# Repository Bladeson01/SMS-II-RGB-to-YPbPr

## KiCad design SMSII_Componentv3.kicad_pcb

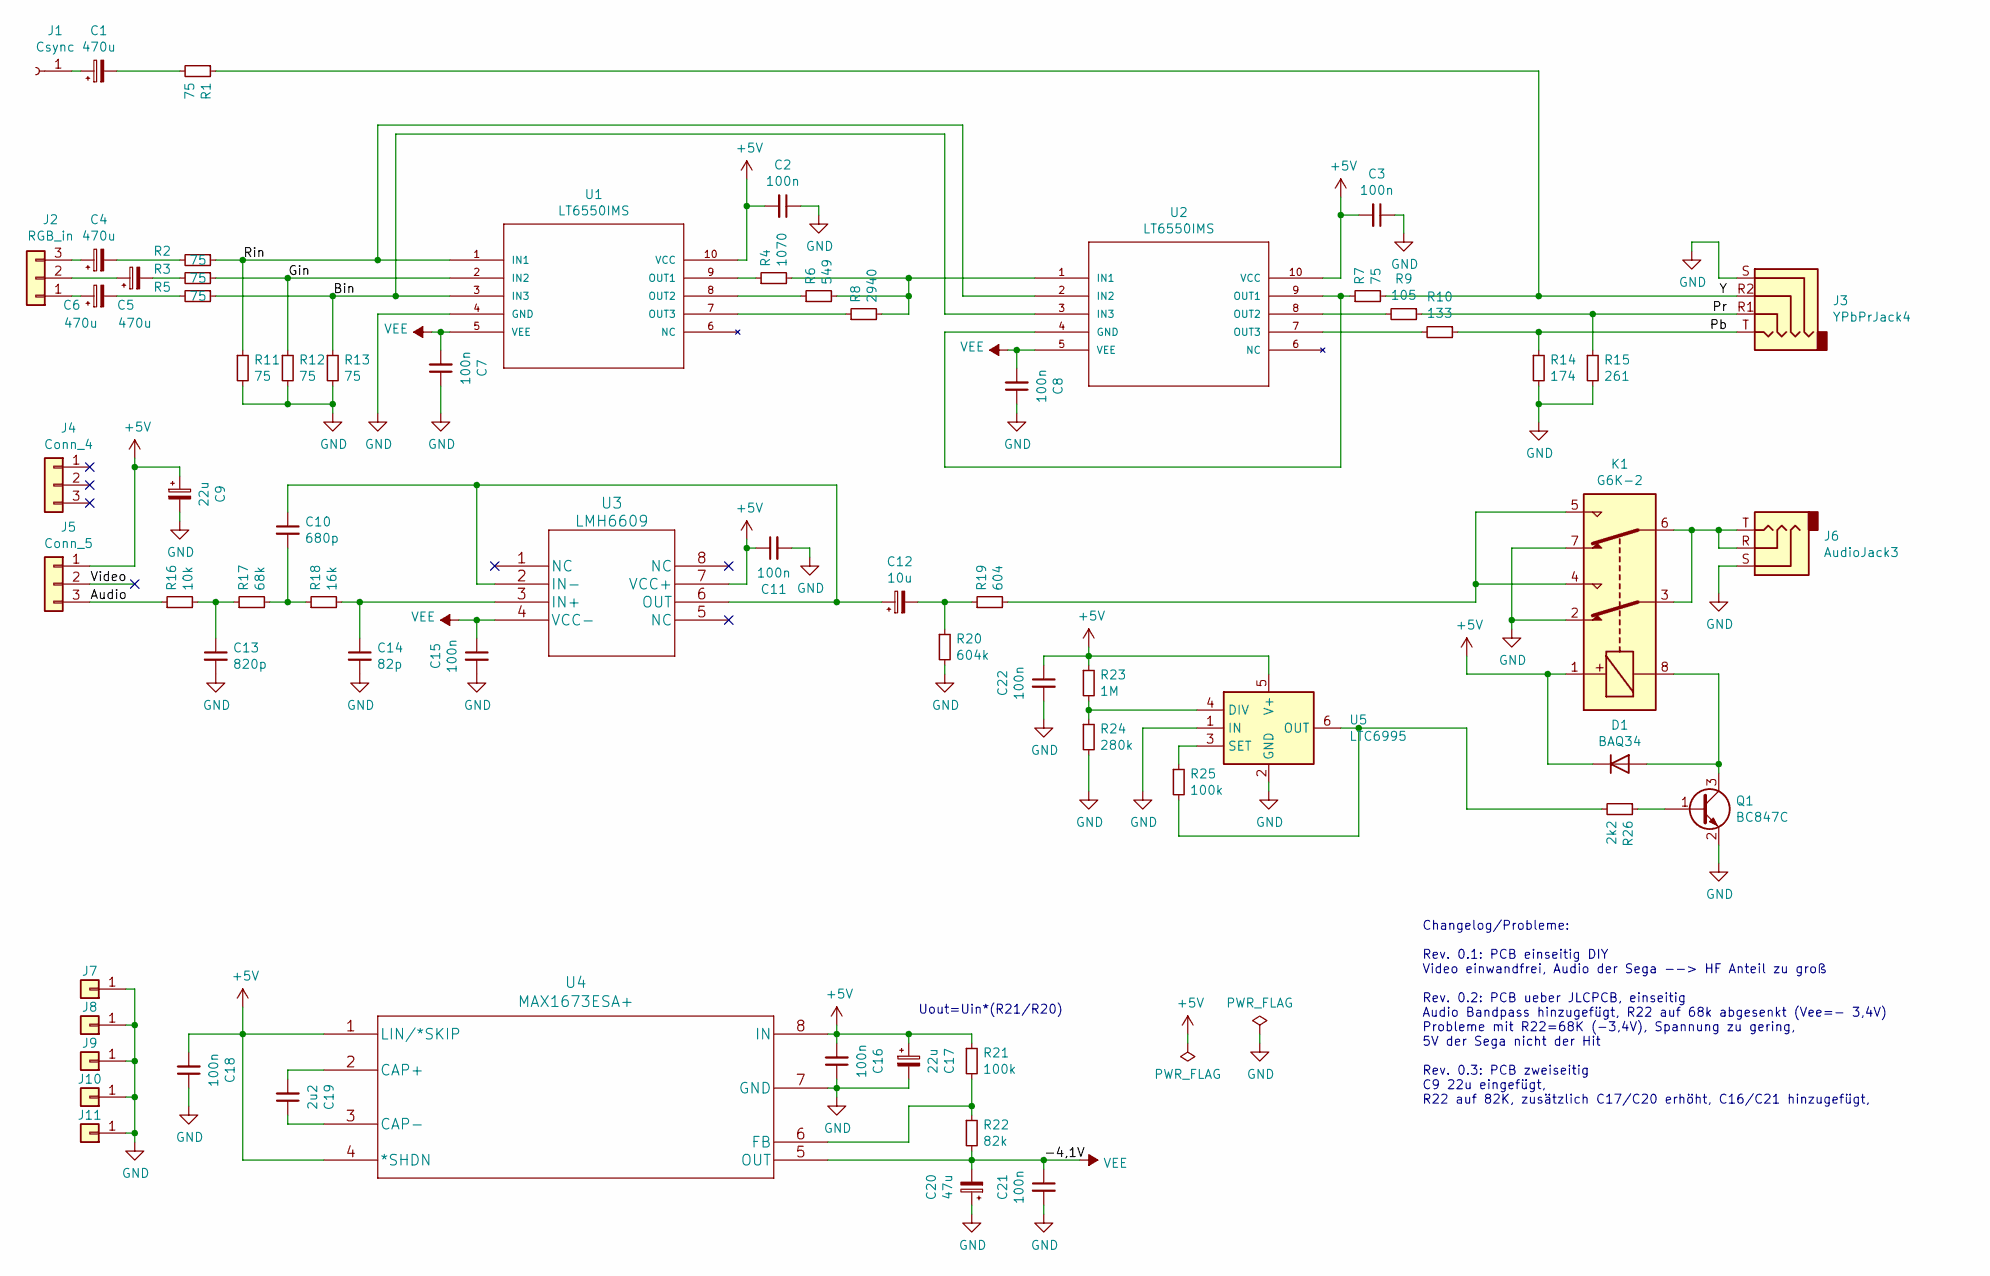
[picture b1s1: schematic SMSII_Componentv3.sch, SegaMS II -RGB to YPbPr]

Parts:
C1, C4, C5, C6: 470u; CP_Elec_6.3x7.7; LCSC C344072
C2, C3, C7, C8, C11, C15, C16, C18, C21, C22: 100n; C_0603_1608Metric_Pad1.05x0.95mm_HandSolder; LCSC C1591
C9, C17: 22u; CP_Elec_5x5.8; LCSC C336306
C10: 680p; C_0603_1608Metric_Pad1.05x0.95mm_HandSolder
C12: 10u; CP_Elec_4x5.8; LCSC C343907
C13: 820p; C_0603_1608Metric_Pad1.05x0.95mm_HandSolder
C14: 82p; C_0603_1608Metric_Pad1.05x0.95mm_HandSolder; LCSC C107056
C19: 2u2; C_0603_1608Metric_Pad1.05x0.95mm_HandSolder; LCSC C162273
C20: 47u; CP_Elec_6.3x5.8; LCSC C249507
D1: BAQ34; D_MiniMELF
J1: Csync; TestPoint_Pad_D2.0mm
J2: RGB_in; PinHeader_1x03_P2.54mm_Vertical
J3: YPbPrJack4; Jack_3.5mm_SMT_Lumberg_13
J4: Conn_4; PinHeader_1x03_P2.54mm_Vertical
J5: Conn_5; PinHeader_1x03_P2.54mm_Vertical
J6: AudioJack3; Jack_3.5mm_3p_SMT_Lumberg
J7, J8, J9, J10, J11: GND; PinHeader_1x01_P2.54mm_Vertical
K1: G6K-2; Relay_DPDT_Omron_G6K-2G-Y
Q1: BC847C; SOT-323_SC-70
R1, R2, R3, R5, R7, R11, R12, R13: 75; R_0603_1608Metric_Pad1.05x0.95mm_HandSolder; LCSC C218142
R4: 1070; R_0603_1608Metric_Pad1.05x0.95mm_HandSolder; LCSC C217842
R6: 549; R_0603_1608Metric_Pad1.05x0.95mm_HandSolder; LCSC C218072
R8: 2940; R_0603_1608Metric_Pad1.05x0.95mm_HandSolder; LCSC C217948
R9: 105; R_0603_1608Metric_Pad1.05x0.95mm_HandSolder; LCSC C217685
R10: 133; R_0603_1608Metric_Pad1.05x0.95mm_HandSolder; LCSC C217726
R14: 174; R_0603_1608Metric_Pad1.05x0.95mm_HandSolder; LCSC C217819
R15: 261; R_0603_1608Metric_Pad1.05x0.95mm_HandSolder; LCSC C217913
R16: 10k; R_0603_1608Metric_Pad1.05x0.95mm_HandSolder; LCSC C128781
R17: 68k; R_0603_1608Metric_Pad1.05x0.95mm_HandSolder; LCSC C425645
R18: 16k; R_0603_1608Metric_Pad1.05x0.95mm_HandSolder; LCSC C217760
R19: 604; R_0603_1608Metric_Pad1.05x0.95mm_HandSolder; LCSC C218096
R20: 604k; R_0603_1608Metric_Pad1.05x0.95mm_HandSolder; LCSC C218095
R21: 100k; R_0603_1608Metric_Pad1.05x0.95mm_HandSolder; LCSC C217682
R22: 82k; R_0603_1608Metric_Pad1.05x0.95mm_HandSolder; LCSC C218159
R23: 1M; R_0603_1608Metric_Pad1.05x0.95mm_HandSolder; LCSC C218095
R24: 280k; R_0603_1608Metric_Pad1.05x0.95mm_HandSolder; LCSC C218095
R25: 100k; R_0603_1608Metric_Pad1.05x0.95mm_HandSolder; LCSC C218095
R26: 2k2; R_0603_1608Metric_Pad1.05x0.95mm_HandSolder; LCSC C218095
U1, U2: LT6550IMS; MSOP-10_MS; LCSC C673138
U3: LMH6609; TL971ID; LCSC C1346629
U4: MAX1673ESA+; MAX1673ESA&plus_; LCSC C143369
U5: LTC6995; TSOT-23-6

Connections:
+5V: C2.2, C3.2, C9.1, C11.1, C16.2, C17.1, C18.2, C22.1, D1.1 (K), J5.1, K1.1, R21.1, R23.1, U1.10 (VCC), U2.10 (VCC), U3.7 (VCC+), U4.1 (LIN/*SKIP), U4.4 (*SHDN), U4.8 (IN), U5.5 (V+)
/Audio: J5.3, R16.1
/Bin: R5.1, R13.1, U1.3 (IN3), U2.3 (IN3)
/Gin: R3.1, R12.1, U1.2 (IN2)
/Pb: J3.T, R10.1, R14.1
/Pr: J3.R1, R9.1, R15.1
/Rin: R2.1, R11.1, U1.1 (IN1), U2.2 (IN2)
/Video: J5.2
/Y: J3.R2, R1.1, R7.2
GND: C2.1, C3.1, C7.1, C8.1, C9.2, C11.2, C13.2, C14.2, C15.2, C16.1, C17.2, C18.1, C20.1, C21.2, C22.2, J3.S, J6.S, J7.1, J8.1, J9.1, J10.1, J11.1, K1.2, K1.7, Q1.2 (E), R11.2, R12.2, R13.2, R14.2, R15.2, R20.2, R24.2, U1.4 (GND), U4.7 (GND), U5.1 (IN), U5.2 (GND)
unnamed: C1.1, J1.1
unnamed: C1.2, R1.2
unnamed: C4.1, J2.3
unnamed: C4.2, R2.2
unnamed: C5.1, J2.2
unnamed: C5.2, R3.2
unnamed: C6.1, J2.1
unnamed: C6.2, R5.2
unnamed: C10.1, C12.1, U3.2 (IN-), U3.6 (OUT)
unnamed: C10.2, R17.2, R18.1
unnamed: C12.2, R19.1, R20.1
unnamed: C13.1, R16.2, R17.1
unnamed: C14.1, R18.2, U3.3 (IN+)
unnamed: C19.1, U4.3 (CAP-)
unnamed: C19.2, U4.2 (CAP+)
unnamed: D1.2 (A), K1.8, Q1.3 (C)
unnamed: J6.R, J6.T, K1.3, K1.6
unnamed: K1.4, K1.5, R19.2
unnamed: Q1.1 (B), R26.1
unnamed: R4.1, U1.9 (OUT1)
unnamed: R4.2, R6.2, R8.2, U2.1 (IN1)
unnamed: R6.1, U1.8 (OUT2)
unnamed: R7.1, U2.4 (GND), U2.9 (OUT1)
unnamed: R8.1, U1.7 (OUT3)
unnamed: R9.2, U2.8 (OUT2)
unnamed: R10.2, U2.7 (OUT3)
unnamed: R21.2, R22.1, U4.6 (FB)
unnamed: R23.2, R24.1, U5.4 (DIV)
unnamed: R25.1, U5.3 (SET)
unnamed: R25.2, R26.2, U5.6 (OUT)
VEE: C7.2, C8.2, C15.1, C20.2, C21.1, R22.2, U1.5 (VEE), U2.5 (VEE), U3.4 (VCC-), U4.5 (OUT)

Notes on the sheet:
Uout=Uin*(R21/R20)
Changelog/Probleme: Rev. 0.1: PCB einseitig DIY Video einwandfrei, Audio der Sega --> HF Anteil zu groß Rev. 0.2: PCB ueber JLCPCB, einseitig Audio Bandpass hinzugefügt, R22 auf 68k abgesenkt (Vee=- 3,4V) Probleme mit R22=68K (-3,4V), Spannung zu gering, 5V der Sega nicht der Hit Rev. 0.3: PCB zwei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

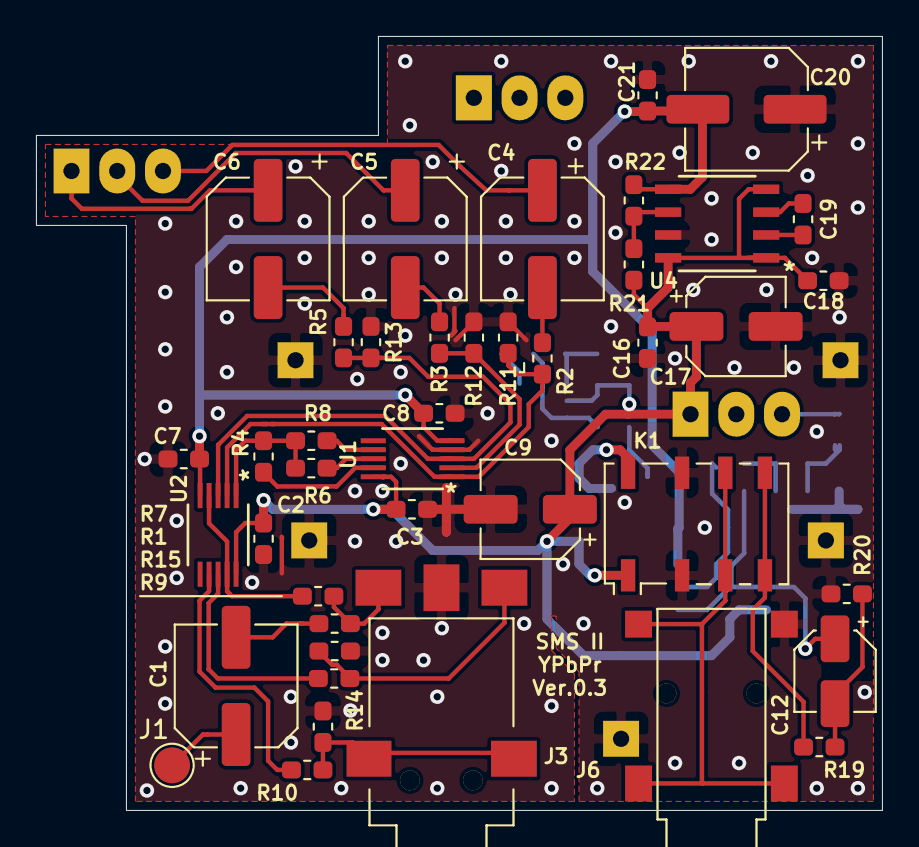
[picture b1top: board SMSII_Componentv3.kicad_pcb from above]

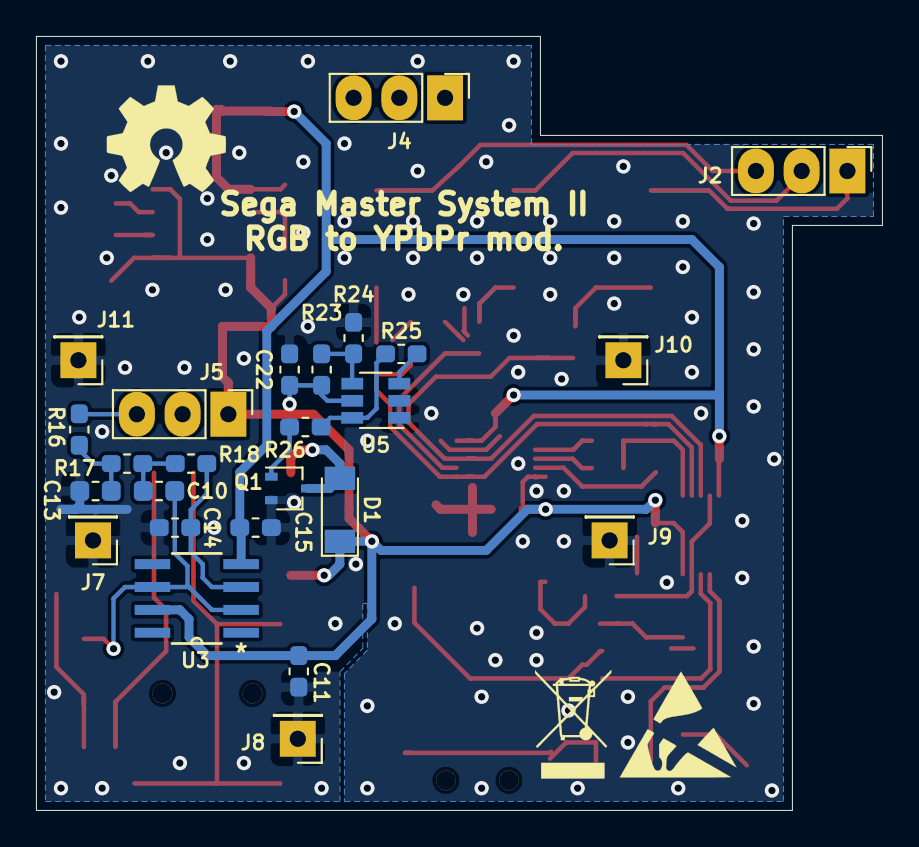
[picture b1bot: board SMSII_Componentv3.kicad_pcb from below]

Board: 2 copper layers, 47.0 x 43.0 mm, 67 parts (25 on the bottom side), 40 nets.

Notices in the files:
parts and their libraries:
Copyright 2016 Accelerated Designs. All rights reserved.
Copyright C 2016 Accelerated Designs. All rights reserved
